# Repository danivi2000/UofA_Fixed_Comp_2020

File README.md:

# UofA_Fixed_Comp_2020
EEG, Body Tracking, Eye Tracking

## Hardware 
### Acquisition Main
#### HackEEG
https://github.com/adamfeuer/hackeeg-shield/tree/master/docs
#### OpenBCI
https://github.com/OpenBCI/V3_Hardware_Design_Files
#### PolyCortex
https://github.com/PolyCortex/AcquisitionEEG
#### Merlin
https://github.com/merlin-neurotech/Hardware-Team

### PCB + Circuit Design
https://www.instructables.com/id/PCB-Creation-with-Eagle-for-Beginners/

### Other
#### Electrodes
https://users.dcc.uchile.cl/~peortega/ae/

## Data Acquisition and UI
### PyQt and LSL App
https://github.com/labstreaminglayer/App-SigVisualizer

## Body Tracking
### Arducam
https://github.com/ArduCAM

### Extras
#### MINT
https://github.com/UBCMint/MINT_FixedChallenge_2019
#### Hackaday
https://hackaday.io/project/13285/logs?sort=oldest

## License
This repository is licensed under the MIT license. See [LICENSE](./LICENSE) for further detail.

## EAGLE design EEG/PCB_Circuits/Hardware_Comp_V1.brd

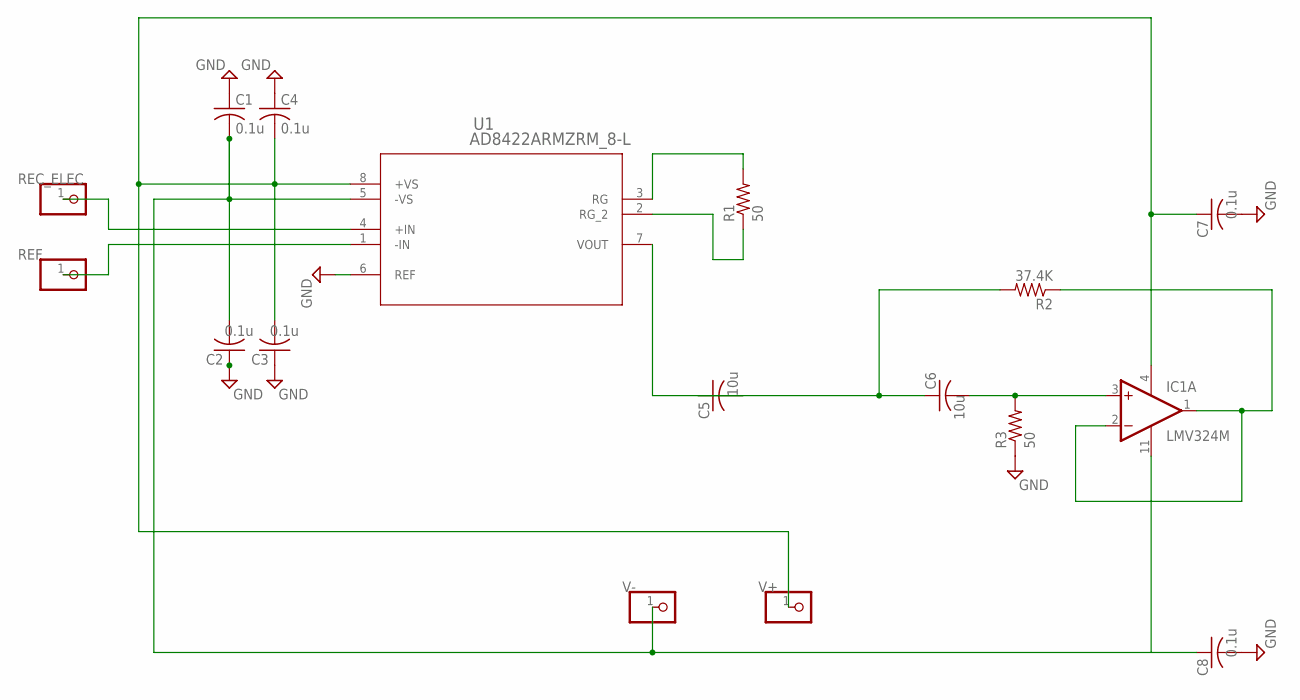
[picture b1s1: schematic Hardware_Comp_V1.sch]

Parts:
9V-: PINHD-1X1; 1X01
C1, C2, C3, C4, C7, C8: 0.1u; C0603
C5, C6: 10u; C0603
IC1: LMV324M; SO14
JP1, JP2, JP3: PINHD-1X1; 1X01
R1, R3: 50; R0603
R2: 37.4K; R0603
U1: AD8422ARMZRM_8-L; RM_8-L

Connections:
GND: C1.1, C2.1, C3.1, C4.1, C7.2, C8.2, R3.1, U1.6 (REF)
unnamed: C5.2, U1.7 (VOUT)
unnamed: C5.1, C6.1, R2.2
unnamed: C6.2, IC1.3 (+IN), R3.2
unnamed: IC1.1 (OUT), IC1.2 (-IN), R2.1
unnamed: R1.2, U1.3 (RG)
unnamed: R1.1, U1.2 (RG_2)
REC_ELEC: JP1.1, U1.4 (+IN)
REF: JP2.1, U1.1 (-IN)
V+: 9V-.1, C3.2, C4.2, C7.1, IC1.4 (V+), U1.8 (+VS)
V+1: C8.1
V-: C1.2, C2.2, IC1.11 (V-), JP3.1, U1.5 (-VS)

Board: 2 copper layers, 17 parts (0 on the bottom side), 11 nets, no tracks yet.

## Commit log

2020-02-20 proof of concept lsl
2020-02-20 added a submodule
2020-02-24 channels in different colors
2020-02-24 ui files added
2020-02-24 add chevron icons and fix excessive hardcoding
2020-02-24 ui now functional
2020-02-24 streams work now
2020-02-24 cleaned up code style
2020-02-24 removed binaries
2020-02-24 removed .DS_STORE
2020-02-24 removed unnecessary files
2020-02-24 Create LICENSE
2020-02-28 finally figured out the toolbar
2020-02-28 changed eeg signal visualizer to dark mode
2020-02-28 refactored code and created new MenuWindow class file
2020-02-28 refactored imports and code
2020-02-28 removed files
2020-02-28 fixed file heirarchy
2020-02-28 removed icon
2020-02-28 created gitignore
2020-02-28 updated stuff
2020-02-28 no longer crashes for missing stream
2020-02-29 added error popup if no streams present
2020-02-29 removed unnecessary file
2020-02-29 made check boxes into clickable buttons
2020-02-29 basic 3d render scene with screen rotation
2020-02-29 mouse translation
2020-02-29 render sphere for head
2020-02-29 changed sphere rotation
2020-03-02 CHECKBOXES LET'S GO
2020-03-02 refactored for better readability
2020-03-02 zoom
2020-03-08 added body tracking
2020-03-08 added alias
2020-03-08 spelling
2020-03-08 altered function name
2020-03-09 New shcematic
2020-03-09 added threaded streams
2020-03-09 uncommented cameras
